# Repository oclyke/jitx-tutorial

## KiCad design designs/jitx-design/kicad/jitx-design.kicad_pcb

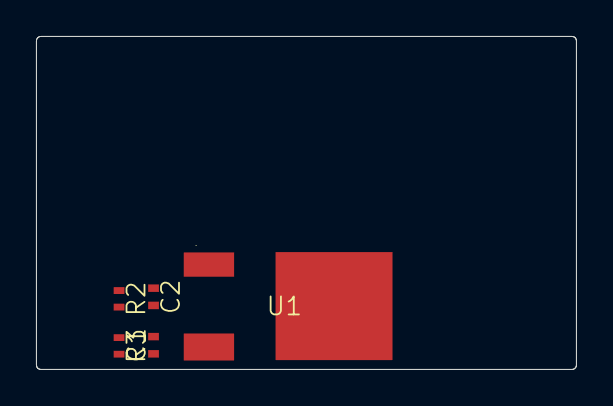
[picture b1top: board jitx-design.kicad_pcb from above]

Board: 4 copper layers, 30.0 x 18.5 mm, 6 parts (1 on the bottom side), 4 nets, no tracks yet.

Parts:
C1: 100n; Pkg0402_1
C2: 1u; Pkg0402_1
R2: 442R; Pkg0402
R3: 270R; Pkg0402
TXT1: TEXT_LP
U1: C75510_LP

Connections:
adj: R2.2, R3.1, U1.1
input: C1.1, U1.3
output: C2.1, R2.1, U1.4
r-lo_p2: C1.2, C2.2, R3.2

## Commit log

2023-12-24 finish tutorial
